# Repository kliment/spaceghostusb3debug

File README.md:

# Space Ghost Host to Host
This is a fun little adapter that converts 2x *USB3 A-B cables* to a USB3.0 specification section 5.5.2 compliant *host-host debug cable*.

# BOM

## Either:
`2x Pulse Electronic E8199-030-01 digikey PN 553-2263-ND`
## Or:
`2x XKB Enterprise U235-091N-4BLRC16-2-5 LCSC PN C388653`

# Images

# Manufacturing
Use the gerbers in the zip file. Designed to match JLC's JLC7628 stackup with 4 layers.

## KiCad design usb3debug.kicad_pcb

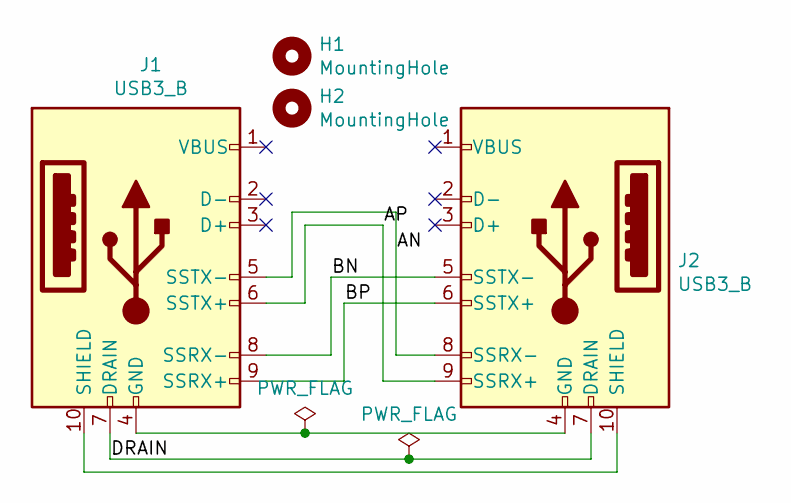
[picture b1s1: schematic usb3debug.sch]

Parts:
H1, H2: MountingHole; MountingHole_3.2mm_M3
J1, J2: USB3_B; USB3-TypeB-U235-091N-4BLRC16-2-5

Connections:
/AN: J1.5 (SSTX-), J2.8 (SSRX-)
/AP: J1.6 (SSTX+), J2.9 (SSRX+)
/BN: J1.8 (SSRX-), J2.5 (SSTX-)
/BP: J1.9 (SSRX+), J2.6 (SSTX+)
/DRAIN: J1.7 (DRAIN), J2.7 (DRAIN)
unnamed: J1.4 (GND), J2.4 (GND)
unnamed: J1.10 (SHIELD), J2.10 (SHIELD)

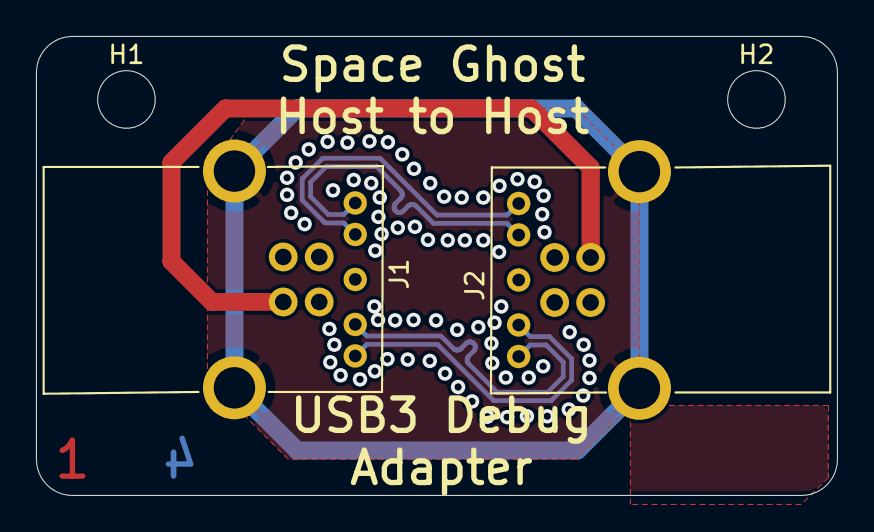
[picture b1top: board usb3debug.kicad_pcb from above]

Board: 4 copper layers, 44.5 x 25.5 mm, 4 parts (0 on the bottom side), 7 nets.

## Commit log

2020-06-08 Initial commit - add schematic and layout
2020-06-08 add gerbers
2020-06-08 Add some documentation
2020-06-08 Add manufacturing information
2020-06-08 fix readme formatting
